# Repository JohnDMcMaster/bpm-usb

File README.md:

# bpm-usb
BP Microsystems USB adapter

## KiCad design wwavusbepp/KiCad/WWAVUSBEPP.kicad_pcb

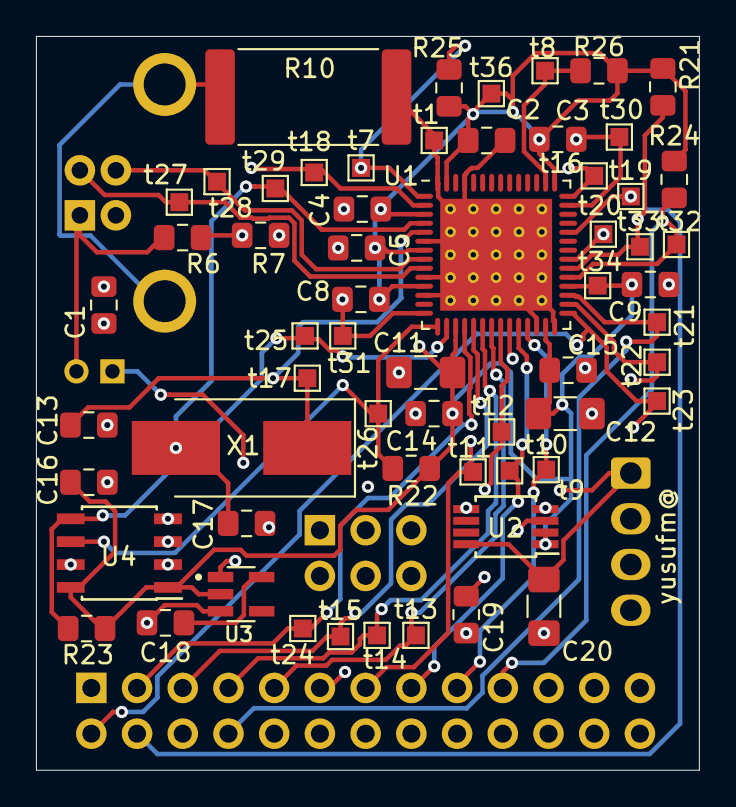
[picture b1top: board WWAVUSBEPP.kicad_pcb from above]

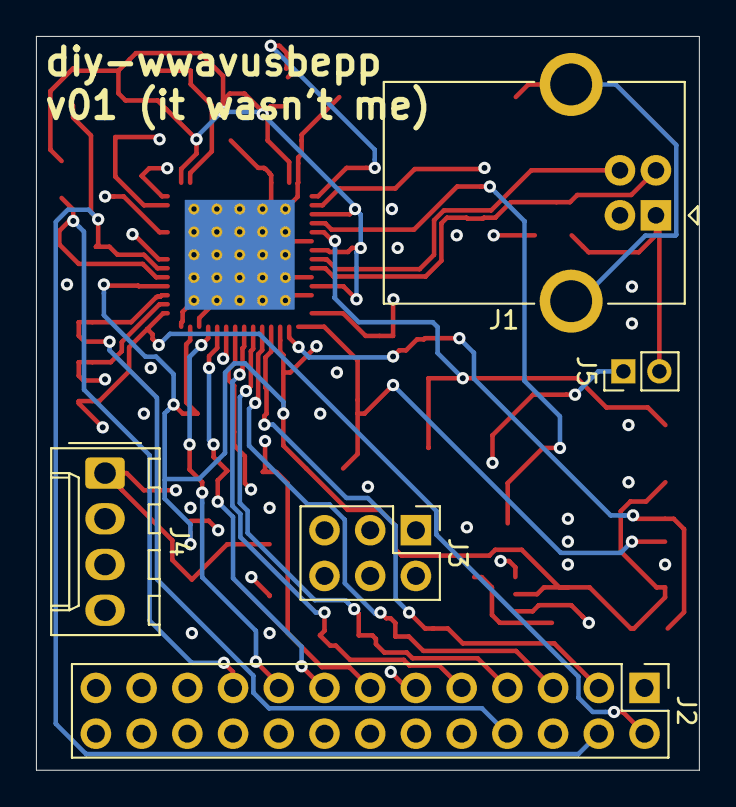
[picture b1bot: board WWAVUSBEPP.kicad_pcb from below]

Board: 4 copper layers, 36.8 x 40.8 mm, 66 parts (5 on the bottom side), 34 nets.

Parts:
C1: 4.7nF; C_0805_2012Metric_Pad1.15x1.40mm_HandSolder
C2, C3, C4, C5, C8, C9, C12, C14, C16, C18, C19: 100nF; C_0805_2012Metric_Pad1.15x1.40mm_HandSolder
C11: 2.2uF; C_1206_3216Metric_Pad1.42x1.75mm_HandSolder
C13, C17: 12pF; C_0805_2012Metric_Pad1.15x1.40mm_HandSolder
C15, C20: 10uF; C_1206_3216Metric_Pad1.42x1.75mm_HandSolder
J1: USB_B; USB_B_OST_USB-B1HSxx_Horizontal
J2: Conn_01x26_Female; PinHeader_2x13_P2.54mm_Vertical
J3: Conn_01x06_Female; PinHeader_2x03_P2.54mm_Vertical
J4: Conn_01x04_Male; Molex_KK-254_AE-6410-04A_1x04_P2.54mm_Vertical
J5: Conn_01x02_Male; PinHeader_1x02_P2.00mm_Vertical
R6: 15.1k; R_0805_2012Metric_Pad1.15x1.40mm_HandSolder
R7: 5.1k; R_0805_2012Metric_Pad1.15x1.40mm_HandSolder
R10: 1M; R_4020_10251Metric_Pad1.65x5.30mm_HandSolder
R21, R24, R25, R26: 10k; R_0805_2012Metric_Pad1.15x1.40mm_HandSolder
R22, R23: 2.2k; R_0805_2012Metric_Pad1.15x1.40mm_HandSolder
U1: CY7C68013-56LFC; Cypress_QFN-56-1EP_8x8mm_P0.5mm_EP6.22x6.22mm_ThermalVias
U2: LT1762-3.3; MSOP-8_3x3mm_P0.65mm
U3: NCP302LSN45T1G; SOP95P275X110-5N
U4: FM24C64B; SOIC-8_3.9x4.9mm_P1.27mm
X1: 24Mhz; Crystal_SMD_7050-2Pin_7.0x5.0mm_HandSoldering
t1, t7, t8, t9, t10, t11, t12, t13, t14, t15, t16, t17, t18, t19, t20, t21, t22, t23, t24, t25, t26, t27, t28, t29, t30, t31, t32, t33, t34, t36: TestPoint; TestPoint_Pad_1.0x1.0mm

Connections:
1: J2.1, U1.30, t22.1
2: J2.2, U1.29, t23.1
3: J2.3, U1.18, t24.1
5: J2.5, U1.19, t15.1
6: J2.6, U1.38, t19.1
7: J2.7, U1.20, t14.1
8: J2.8, U1.31, t21.1
9: J2.9, U1.21, t13.1
11: J2.11, U1.22, t12.1
13: J2.13, U1.23, t11.1
15: J2.15, U1.24, t10.1
17: J2.17, U1.25, t9.1
23: J2.23, U1.2, t18.1
25: J2.25, U1.35, t20.1
+3V3: C2.2, C3.2, C4.1, C5.1, C8.2, C9.2, C11.1, C12.2, C14.2, C15.1, C16.2, C19.1, R21.1, R22.1, R23.1, R24.1, R25.1, R26.2, U1.3, U1.7, U1.11, U1.17, U1.27, U1.32, U1.43, U1.55, U2.1, U2.2, U3.2, U4.1, U4.8, t34.1, t36.1
D+: J1.3, U1.8, t28.1
D-: J1.2, U1.9, t27.1
Earth: C1.1, C2.1, C3.1, C4.2, C5.2, C8.1, C9.1, C11.2, C12.1, C13.2, C14.1, C15.2, C16.1, C17.2, C18.2, C20.2, J2.10, J2.12, J2.14, J2.16, J2.18, J2.20, J2.22, J2.24, J2.26, J4.2, R7.1, R10.1, U1.6, U1.10, U1.12, U1.14, U1.26, U1.28, U1.41, U1.53, U1.56, U1.57, U2.4, U3.3, U4.2, U4.3, U4.4, U4.7, t1.1, t30.1, t31.1
unnamed: C1.2, J1.4
unnamed: C18.1, U3.5
unnamed: C19.2, U2.3
unnamed: C20.1, J4.1, J5.1, U2.8
unnamed: J1.1, J5.2, R6.2
unnamed: J1.5, R10.2
unnamed: J2.4, R21.2, U1.34, t33.1
unnamed: J2.19, R24.2, U1.33, t32.1
unnamed: J2.21, R25.2, U1.1, t7.1
unnamed: R6.1, R7.2, U2.5
unnamed: R26.1, U1.44, t8.1
SCL: R22.2, U1.15, U4.6, t26.1
SDA: R23.2, U1.16, U4.5, t25.1
U3_R: U1.42, U3.1, t16.1
XTALIN: C13.1, U1.5, X1.1, t17.1
XTALOUT: C17.1, U1.4, X1.2, t29.1

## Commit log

2018-09-17 Import BPM schematic
2018-09-17 Add .png to make viewing easier
2019-05-06 Creating KiCad project and commiting initial version of schematic.
2019-05-14 Started layout.
2019-05-15 Fixes to schematic and renaming components to match website image info.
2019-05-18 Fixed one footprint, and restarted traces.
2019-05-20 Updates to routes, not complete.
2019-05-21 Completed traces, not silk.
2019-05-21 Added jumper J5, and fixed some resistor values, and colocated cap next to U4.
2019-05-31 Added testpoints and rerouted some tracks. Work in progress.
2019-06-01 routing complete.
2019-06-01 Fixed the R10 resistor footprint and rerouting. No silkscreen changes done.
2019-06-01 Finished routing, silk, etc. Should be complete.
2019-08-01 wwavusbepp: small tweaks, "diy" silkscreen
2019-08-01 Remove .bak file
2019-08-01 Remove obsolete PCB123 files
2019-08-01 Simplify file paths
